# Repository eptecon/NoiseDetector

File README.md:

NoiseDetector: Connected Noise Detector
======

Noise Detector is a simple device for lowering noise levels in the office or public places. It monitors noise level and alarms when it gets too loud. It is also connected to cloud over Wireless LAN for providing noise data for further analytics
It is easy to install and use in every environment.

### Hardware

Noise Detector is based on a MEMS microphone that measures intensity of noise and ESP32 microcontroller that monitors the noise level and sends measured results to cloud.
The user can adjust a threshold for the detection. The Noise Detector can indicate alarms if it is too loud using onboard buzzer and LED.

### Firmware

The firmware consists of a RTOS and applications for measuring and analysing of noise level as well as sending information to cloud. It connects to a cloud and provides noise data over MQTT.

### Usage

No software installation is required. Just turn on and connect to your WLAN Network. Immediately after connecting, the device starts to send the measured noise level 
to the cloud service ([GlueLogics](https://github.com/eptecon/gluelogics)) enabling analytics for your working environment, even without invasive notifications.

---

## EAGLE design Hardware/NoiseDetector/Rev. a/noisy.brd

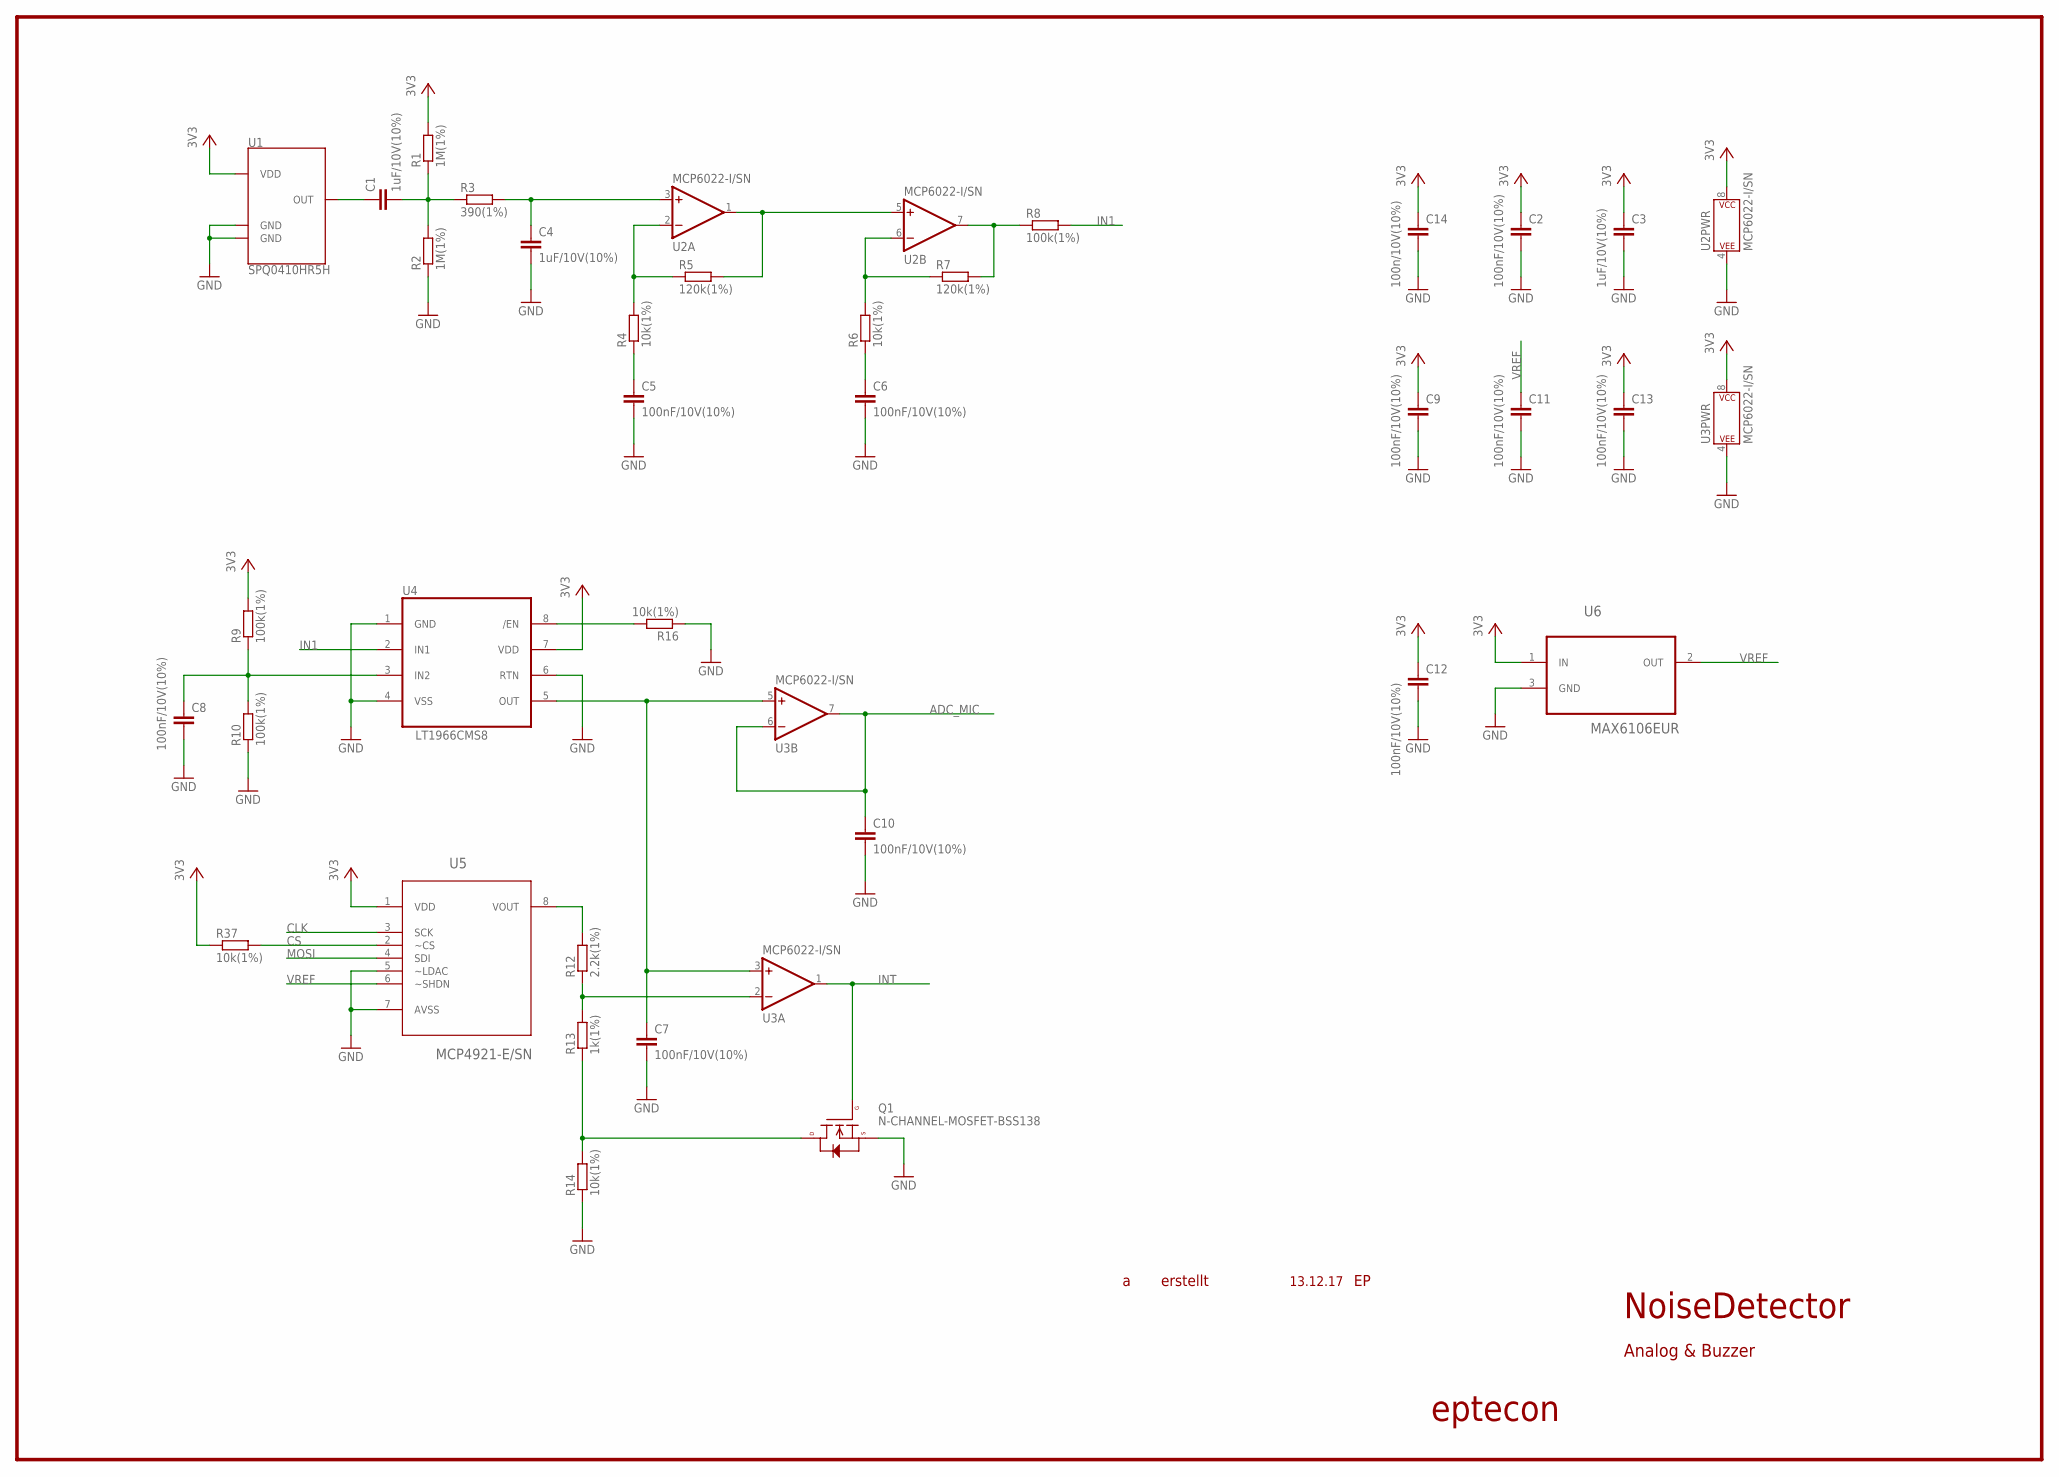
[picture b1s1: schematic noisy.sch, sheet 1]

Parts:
C1, C3, C4: 1uF/10V(10%); C0603
C2, C5, C6, C7, C8, C9, C10, C11, C12, C13: 100nF/10V(10%); C0603
C14: 100n/10V(10%); C0603
Q1: N-CHANNEL-MOSFET-BSS138; SOT23-3
R1, R2: 1M(1%); R0603
R3: 390(1%); R0603
R4, R6, R14, R16, R37: 10k(1%); R0603
R5, R7: 120k(1%); R0603
R8, R9, R10: 100k(1%); R0603
R12: 2.2k(1%); R0603
R13: 1k(1%); R0603
U1: SPQ0410HR5H; SPQ0410HR
U2, U3: MCP6022-I/SN; SOIC08
U4: LT1966CMS8; MSOP8
U5: MCP4921-E/SN; SOIC8-N_MC
U6: MAX6106EUR; SOT23-3

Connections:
3V3: C2.1, C3.1, C9.1, C12.1, C13.1, C14.1, R1.2, R9.2, R37.1, U1.P$1 (VDD), U2.8 (P$V+), U3.8 (P$V+), U4.7 (VDD), U5.1 (VDD), U6.1 (IN); also elsewhere on the board
ADC_MIC: C10.1, U3.6 (-IN), U3.7 (OUT); also elsewhere on the board
CLK: U5.3 (SCK); also elsewhere on the board
CS: R37.2, U5.2 (~CS); also elsewhere on the board
GND: C2.2, C3.2, C4.2, C5.2, C6.2, C7.2, C8.2, C9.2, C10.2, C11.2, C12.2, C13.2, C14.2, Q1.2 (S), R2.1, R10.1, R14.1, R16.1, U1.P$2 (GND), U1.P$3 (GND), U2.4 (P$V-), U3.4 (P$V-), U4.1 (GND), U4.4 (VSS), U4.6 (RTN), U5.5 (~LDAC), U5.7 (AVSS), U6.3 (GND); also elsewhere on the board
IN1: R8.2, U4.2 (IN1)
INT: Q1.1 (G), U3.1 (OUT); also elsewhere on the board
MOSI: U5.4 (SDI); also elsewhere on the board
unnamed: C1.1, U1.P$4 (OUT)
unnamed: C1.2, R1.1, R2.2, R3.1
unnamed: C4.1, R3.2, U2.3 (+IN)
unnamed: R4.2, R5.1, U2.2 (-IN)
unnamed: C5.1, R4.1
unnamed: R5.2, U2.1 (OUT), U2.5 (+IN)
unnamed: R6.2, R7.1, U2.6 (-IN)
unnamed: C6.1, R6.1
unnamed: R7.2, R8.1, U2.7 (OUT)
unnamed: C8.1, R9.1, R10.2, U4.3 (IN2)
unnamed: R12.2, U5.8 (VOUT)
unnamed: R12.1, R13.2, U3.2 (-IN)
unnamed: Q1.3 (D), R13.1, R14.2
unnamed: C7.1, U3.3 (+IN), U3.5 (+IN), U4.5 (OUT)
unnamed: R16.2, U4.8 (/EN)
VREF: C11.1, U5.6 (~SHDN), U6.2 (OUT)

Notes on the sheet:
NoiseDetector
Analog & Buzzer
eptecon
erstellt
13.12.17

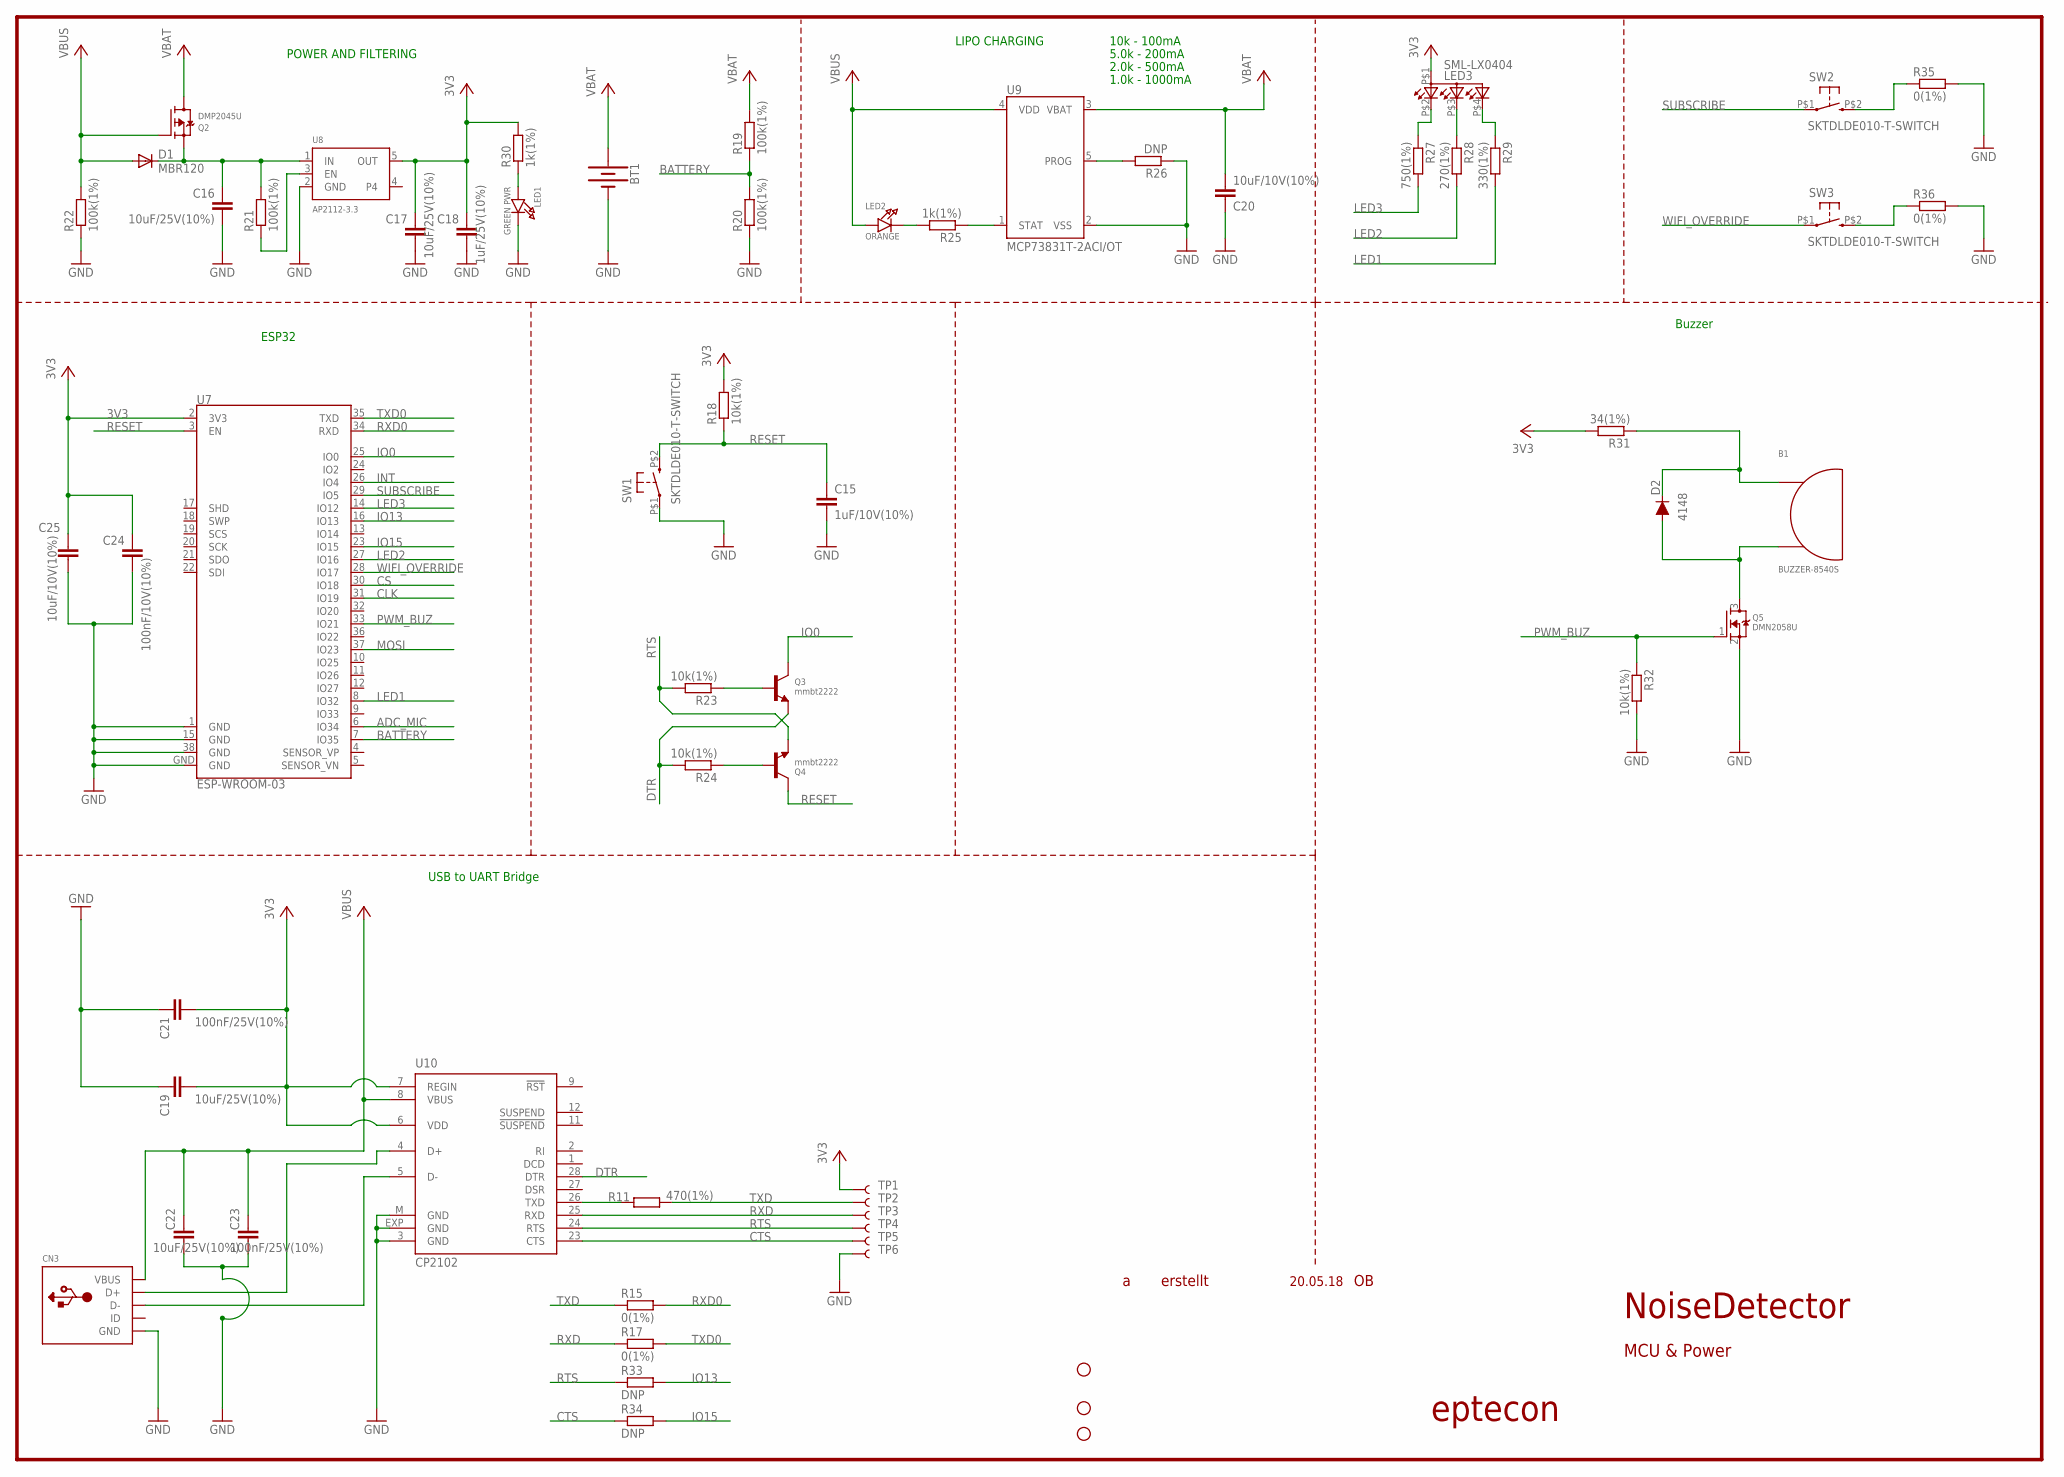
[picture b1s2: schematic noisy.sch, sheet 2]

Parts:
B1: BUZZER-8540S
BT1: BATTERY-AA
C15: 1uF/10V(10%); C0603
C16, C17, C19, C22: 10uF/25V(10%); C0603
C18: 1uF/25V(10%); C0603
C20, C25: 10uF/10V(10%); C0603
C21, C23: 100nF/25V(10%); C0603
C24: 100nF/10V(10%); C0603
CN3: USBMINIBLARGE; USB-MINIB_LARGER
D1: MBR120; SOD123
D2: 4148; SOD-323
H1, H2, H3: STAND-OFF
LED1: GREEN PWR; CHIPLED_0805_NOOUTLINE
LED2: ORANGE; CHIPLED_0805_NOOUTLINE
LED3: SML-LX0404; LED_RGB
Q2: DMP2045U; SOT23-R
Q3, Q4: mmbt2222; SOT23-R
Q5: DMN2058U; SOT23-R
R11: 470(1%); R0603
R15, R17, R35, R36: 0(1%); R0603
R18, R23, R24, R32: 10k(1%); R0603
R19, R20, R21, R22: 100k(1%); R0603
R25, R30: 1k(1%); R0603
R26, R33, R34: DNP; R0603
R27: 750(1%); R0603
R28: 270(1%); R0603
R29: 330(1%); R0603
R31: 34(1%); R0603
SW1, SW2, SW3: SKTDLDE010-T-SWITCH; T-SWITCH-ALPS-2
TP1, TP2, TP3, TP4, TP5, TP6: TEST-POINT3X5; PAD.03X.05
U7: ESP-WROOM-03
U8: AP2112-3.3; SOT23-5
U9: MCP73831T-2ACI/OT; SOT23-5
U10: CP2102; MLP28

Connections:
3V3: C17.1, C18.1, C19.2, C21.2, C24.1, C25.1, LED3.P$1 (A2), R18.2, R30.2, R31.2, TP1.P$1, U7.2 (3V3), U8.5 (OUT), U10.6 (VDD), U10.7 (REGIN); also elsewhere on the board
ADC_MIC: U7.6 (IO34); also elsewhere on the board
BATTERY: R19.1, R20.2, U7.7 (IO35)
CLK: U7.31 (IO19); also elsewhere on the board
CS: U7.30 (IO18); also elsewhere on the board
CTS: R34.1, TP5.P$1, U10.23 (CTS)
DTR: Q3.2 (E), R24.2, U10.28 (DTR)
GND: BT1.GND@1 (-), C15.2, C16.2, C17.2, C18.2, C19.1, C20.1, C21.1, C22.1, C23.1, C24.2, C25.2, CN3.GND, LED1.C, Q5.2 (S), R20.1, R22.1, R26.1, R32.2, R35.2, R36.2, SW1.P$1 (1), TP6.P$1, U7.1 (GND), U7.15 (GND), U7.38 (GND), U7.GND, U8.2 (GND), U9.2 (VSS), U10.3 (GND), U10.EXP (GND), U10.M (GND); also elsewhere on the board
INT: U7.26 (IO4); also elsewhere on the board
IO0: Q3.3 (C), U7.25 (IO0)
IO13: R33.2, U7.16 (IO13)
IO15: R34.2, U7.23 (IO15)
LED1: R29.2, U7.8 (IO32)
LED2: R28.2, U7.27 (IO16)
LED3: R27.2, U7.14 (IO12)
MOSI: U7.37 (IO23); also elsewhere on the board
unnamed: C16.1, D1.C, Q2.2 (S), R21.2, U8.1 (IN)
unnamed: Q4.1 (B), R24.1
unnamed: R11.1, U10.26 (TXD)
unnamed: Q3.1 (B), R23.1
unnamed: CN3.D+, U10.4 (D+)
unnamed: CN3.D-, U10.5 (D-)
unnamed: R35.1, SW2.P$2 (3)
unnamed: R36.1, SW3.P$2 (3)
unnamed: LED3.P$2 (CRED), R27.1
unnamed: R25.1, U9.1 (STAT)
unnamed: LED2.C, R25.2
unnamed: LED3.P$3 (CBLUE), R28.1
unnamed: LED3.P$4 (CGREEN), R29.1
unnamed: R26.2, U9.5 (PROG)
unnamed: R21.1, U8.3 (EN)
unnamed: LED1.A, R30.1
unnamed: B1.PLUS, D2.C, R31.1
unnamed: B1.MINUS, D2.A, Q5.3 (D)
PWM_BUZ: Q5.1 (G), R32.1, U7.33 (IO21)
RESET: C15.1, Q4.3 (C), R18.1, SW1.P$2 (3), U7.3 (EN)
RTS: Q4.2 (E), R23.2, R33.1, TP4.P$1, U10.24 (RTS)
RXD: R17.1, TP3.P$1, U10.25 (RXD)
RXD0: R15.2, U7.34 (RXD)
SUBSCRIBE: SW2.P$1 (1), U7.29 (IO5)
TXD: R11.2, R15.1, TP2.P$1
TXD0: R17.2, U7.35 (TXD)
VBAT: BT1.PWR@1 (+), C20.2, Q2.3 (D), R19.2, U9.3 (VBAT)
VBUS: C22.2, C23.2, CN3.VBUS, D1.A, LED2.A, Q2.1 (G), R22.2, U9.4 (VDD), U10.8 (VBUS)
WIFI_OVERRIDE: SW3.P$1 (1), U7.28 (IO17)

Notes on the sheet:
NoiseDetector
MCU & Power
eptecon
erstellt
20.05.18
ESP32
POWER AND FILTERING
USB to UART Bridge
LIPO CHARGING
10k - 100mA
5.0k - 200mA
2.0k - 500mA
1.0k - 1000mA
Buzzer

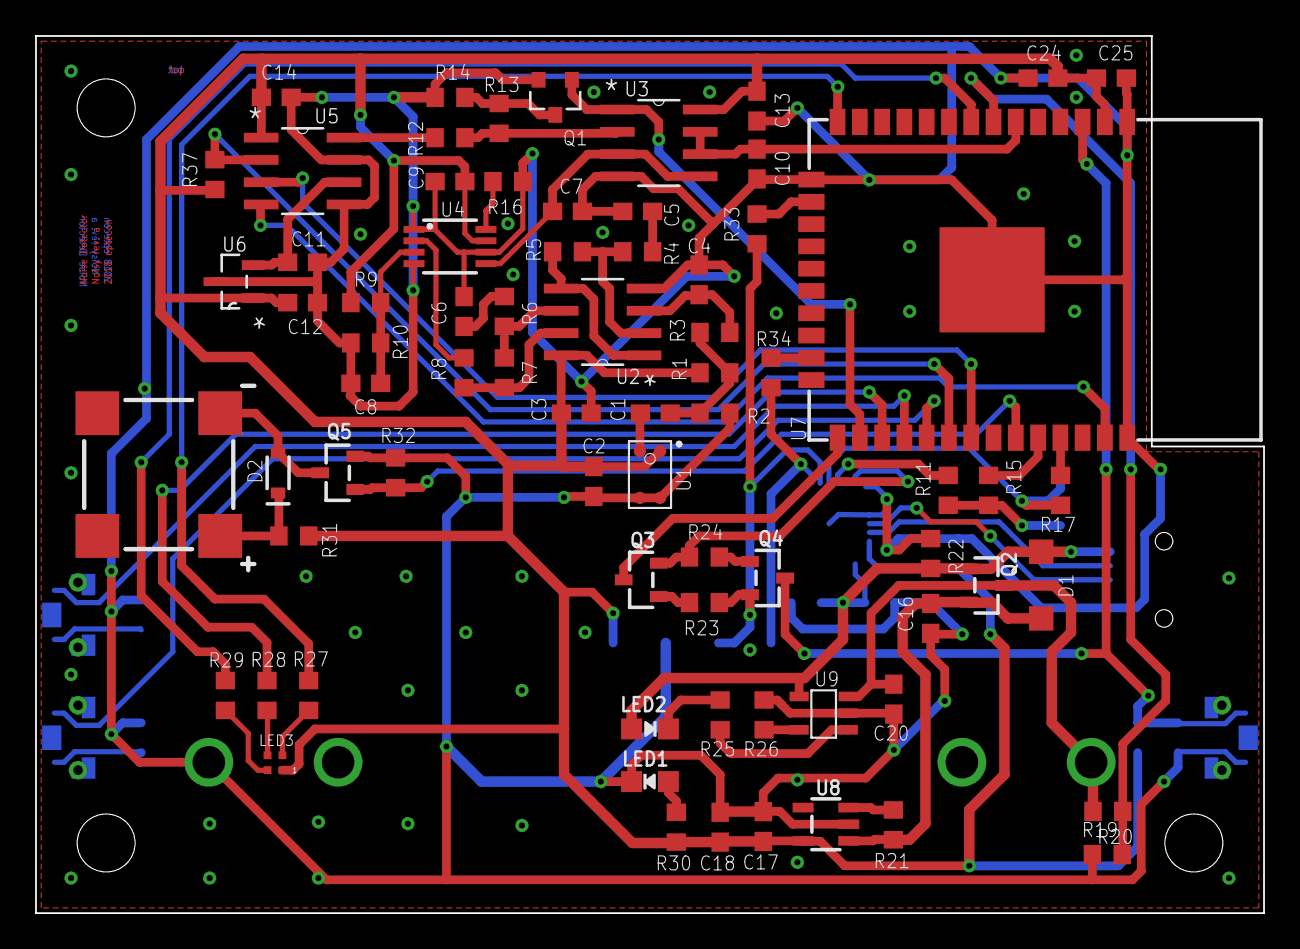
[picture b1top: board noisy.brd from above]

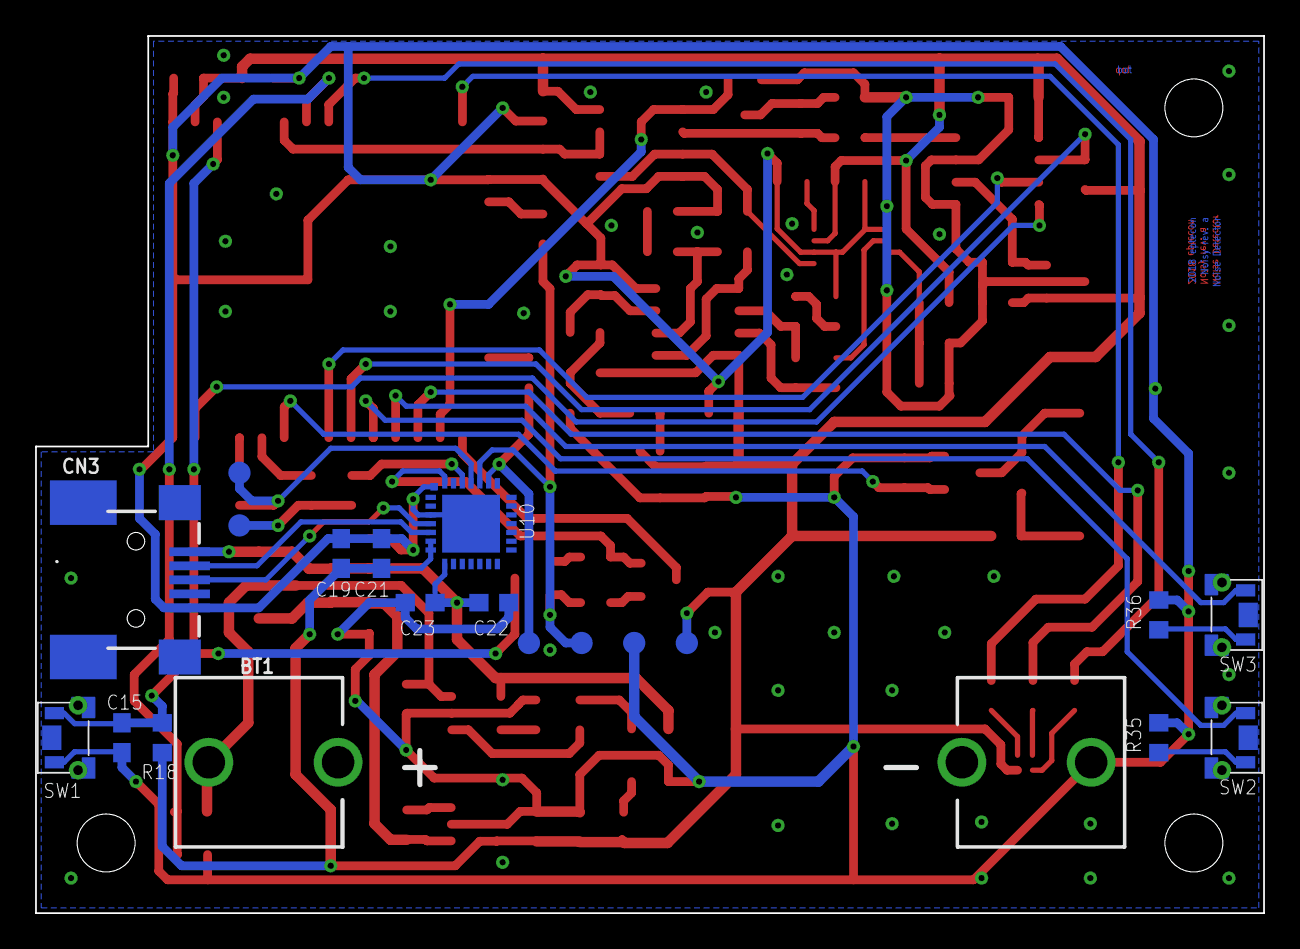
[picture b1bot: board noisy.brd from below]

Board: 2 copper layers, 70.0 x 50.0 mm, 97 parts (20 on the bottom side), 62 nets.

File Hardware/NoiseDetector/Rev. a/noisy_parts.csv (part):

"Part";"Value";"Device";"Package";"Description";"DATASHEET";"DESCRIPTION";"DIGIKEY";"ELEMENT14";"MF";"MPN";"OC_FARNELL";"OC_NEWARK";"OTHER";"PACKAGE";"PROD_ID";"SF_SKU";"SUPPLIER";"URL";"VALUE";
"B1";"BUZZER-8540S";"BUZZER-8540S";"BUZZER-8540S";"";"";"";"";"";"";"";"";"";"";"";"";"";"";"";"";
"BT1";"";"BATTERY-AA";"BATTERY-AA";"Battery - Single Cell";"";"";"";"";"";"";"";"";"";"";"BATT-08316";"PRT-07949";"";"";"";
"C1";"1uF/10V(10%)";"C-EUC0603";"C0603";"CAPACITOR, European symbol";"";"";"";"";"";"";"";"";"";"";"";"";"";"";"";
"C2";"100nF/10V(10%)";"C-EUC0603";"C0603";"CAPACITOR, European symbol";"";"";"";"";"";"";"";"";"";"";"";"";"";"";"";
"C3";"1uF/10V(10%)";"C-EUC0603";"C0603";"CAPACITOR, European symbol";"";"";"";"";"";"";"";"";"";"";"";"";"";"";"";
"C4";"1uF/10V(10%)";"C-EUC0603";"C0603";"CAPACITOR, European symbol";"";"";"";"";"";"";"";"";"";"";"";"";"";"";"";
"C5";"100nF/10V(10%)";"C-EUC0603";"C0603";"CAPACITOR, European symbol";"";"";"";"";"";"";"";"";"";"";"";"";"";"";"";
"C6";"100nF/10V(10%)";"C-EUC0603";"C0603";"CAPACITOR, European symbol";"";"";"";"";"";"";"";"";"";"";"";"";"";"";"";
"C7";"100nF/10V(10%)";"C-EUC0603";"C0603";"CAPACITOR, European symbol";"";"";"";"";"";"";"";"";"";"";"";"";"";"";"";
"C8";"100nF/10V(10%)";"C-EUC0603";"C0603";"CAPACITOR, European symbol";"";"";"";"";"";"";"";"";"";"";"";"";"";"";"";
"C9";"100nF/10V(10%)";"C-EUC0603";"C0603";"CAPACITOR, European symbol";"";"";"";"";"";"";"";"";"";"";"";"";"";"";"";
"C10";"100nF/10V(10%)";"C-EUC0603";"C0603";"CAPACITOR, European symbol";"";"";"";"";"";"";"";"";"";"";"";"";"";"";"";
"C11";"100nF/10V(10%)";"C-EUC0603";"C0603";"CAPACITOR, European symbol";"";"";"";"";"";"";"";"";"";"";"";"";"";"";"";
"C12";"100nF/10V(10%)";"C-EUC0603";"C0603";"CAPACITOR, European symbol";"";"";"";"";"";"";"";"";"";"";"";"";"";"";"";
"C13";"100nF/10V(10%)";"C-EUC0603";"C0603";"CAPACITOR, European symbol";"";"";"";"";"";"";"";"";"";"";"";"";"";"";"";
"C14";"100n/10V(10%)";"C-EUC0603";"C0603";"CAPACITOR, European symbol";"";"";"";"";"";"";"";"";"";"";"";"";"";"";"";
"C15";"1uF/10V(10%)";"C-EUC0603";"C0603";"CAPACITOR, European symbol";"";"";"";"";"";"";"";"";"";"";"";"";"";"";"";
"C16";"10uF/25V(10%)";"C-EUC0603";"C0603";"CAPACITOR, European symbol";"";"";"";"";"";"";"";"";"";"";"";"";"";"";"";
"C17";"10uF/25V(10%)";"C-EUC0603";"C0603";"CAPACITOR, European symbol";"";"";"";"";"";"";"";"";"";"";"";"";"";"";"";
"C18";"1uF/25V(10%)";"C-EUC0603";"C0603";"CAPACITOR, European symbol";"";"";"";"";"";"";"";"";"";"";"";"";"";"";"";
"C19";"10uF/25V(10%)";"C-EUC0603";"C0603";"CAPACITOR, European symbol";"";"";"";"";"";"";"";"";"";"";"";"";"";"";"";
"C20";"10uF/10V(10%)";"C-EUC0603";"C0603";"CAPACITOR, European symbol";"";"";"";"";"";"";"";"";"";"";"";"";"";"";"";
"C21";"100nF/25V(10%)";"C-EUC0603";"C0603";"CAPACITOR, European symbol";"";"";"";"";"";"";"";"";"";"";"";"";"";"";"";
"C22";"10uF/25V(10%)";"C-EUC0603";"C0603";"CAPACITOR, European symbol";"";"";"";"";"";"";"";"";"";"";"";"";"";"";"";
"C23";"100nF/25V(10%)";"C-EUC0603";"C0603";"CAPACITOR, European symbol";"";"";"";"";"";"";"";"";"";"";"";"";"";"";"";
"C24";"100nF/10V(10%)";"C-EUC0603";"C0603";"CAPACITOR, European symbol";"";"";"";"";"";"";"";"";"";"";"";"";"";"";"";
"C25";"10uF/10V(10%)";"C-EUC0603";"C0603";"CAPACITOR, European symbol";"";"";"";"";"";"";"";"";"";"";"";"";"";"";"";
"CN3";"";"USBMINIBLARGE";"USB-MINIB_LARGER";"USB Connectors";"";"";"";"";"";"";"";"";"";"";"";"";"";"";"";
"D1";"MBR120";"MBR0520LT";"SOD123";"SCHOTTKY BARRIER RECTIFIER";"";"";"";"";"";"";"";"";"";"";"";"";"";"";"";
"D2";"4148";"DIODE-BAS16J";"SOD-323";"Diode";"";"";"";"";"";"";"";"";"";"";"DIO-09646";"";"";"";"250mA/100V";
"H1";"STAND-OFF";"STAND-OFF";"STAND-OFF";"Stand Off";"";"";"";"";"";"";"";"";"";"";"";"";"";"";"";
"H2";"STAND-OFF";"STAND-OFF";"STAND-OFF";"Stand Off";"";"";"";"";"";"";"";"";"";"";"";"";"";"";"";
"H3";"STAND-OFF";"STAND-OFF";"STAND-OFF";"Stand Off";"";"";"";"";"";"";"";"";"";"";"";"";"";"";"";
"LED1";"GREEN PWR";"LED0805_NOOUTLINE";"CHIPLED_0805_NOOUTLINE";"LED";"";"";"";"";"";"";"";"";"";"";"";"";"";"";"";
"LED2";"ORANGE";"LED0805_NOOUTLINE";"CHIPLED_0805_NOOUTLINE";"LED";"";"";"";"";"";"";"";"";"";"";"";"";"";"";"";
"LED3";"SML-LX0404";"SML-LX0404";"LED_RGB";"";"";"";"";"";"";"";"";"";"";"";"";"";"";"";"";
"Q1";"N-CHANNEL-MOSFET-BSS138";"N-CHANNEL-MOSFET-BSS138";"SOT23-3";"N-Channel MOSFET Mode Field Effect Transistor";"http://www.fairchildsemi.com/ds/BS/BSS138.pdf";"";"BSS138TR-ND";"2323154";"";"";"";"";"";"";"";"";"";"http://au.element14.com/fairchild-semiconductor/bss138/mosfe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";"";
"Q2";"DMP2045U";"MOSFET-P";"SOT23-R";"P-Channel Mosfet";"";"";"";"";"";"";"";"";"";"";"";"";"";"";"";
"Q3";"mmbt2222";"TRANSISTOR_NPN";"SOT23-R";"NPN Transistor";"";"";"";"";"";"";"";"";"";"";"";"";"";"";"";
"Q4";"mmbt2222";"TRANSISTOR_NPN";"SOT23-R";"NPN Transistor";"";"";"";"";"";"";"";"";"";"";"";"";"";"";"";
"Q5";"DMN2058U";"MOSFET-NREFLOW";"SOT23-R";"N-Channel Mosfet";"";"";"";"";"";"";"";"";"";"";"";"";"";"";"";
"R1";"1M(1%)";"R-EU_R0603";"R0603";"RESISTOR, European symbol";"";"";"";"";"";"";"";"";"";"";"";"";"";"";"";
"R2";"1M(1%)";"R-EU_R0603";"R0603";"RESISTOR, European symbol";"";"";"";"";"";"";"";"";"";"";"";"";"";"";"";
"R3";"390(1%)";"R-EU_R0603";"R0603";"RESISTOR, European symbol";"";"";"";"";"";"";"";"";"";"";"";"";"";"";"";
"R4";"10k(1%)";"R-EU_R0603";"R0603";"RESISTOR, European symbol";"";"";"";"";"";"";"";"";"";"";"";"";"";"";"";
"R5";"120k(1%)";"R-EU_R0603";"R0603";"RESISTOR, European symbol";"";"";"";"";"";"";"";"";"";"";"";"";"";"";"";
"R6";"10k(1%)";"R-EU_R0603";"R0603";"RESISTOR, European symbol";"";"";"";"";"";"";"";"";"";"";"";"";"";"";"";
"R7";"120k(1%)";"R-EU_R0603";"R0603";"RESISTOR, European symbol";"";"";"";"";"";"";"";"";"";"";"";"";"";"";"";
"R8";"100k(1%)";"R-EU_R0603";"R0603";"RESISTOR, European symbol";"";"";"";"";"";"";"";"";"";"";"";"";"";"";"";
"R9";"100k(1%)";"R-EU_R0603";"R0603";"RESISTOR, European symbol";"";"";"";"";"";"";"";"";"";"";"";"";"";"";"";
"R10";"100k(1%)";"R-EU_R0603";"R0603";"RESISTOR, European symbol";"";"";"";"";"";"";"";"";"";"";"";"";"";"";"";
"R11";"470(1%)";"R-EU_R0603";"R0603";"RESISTOR, European symbol";"";"";"";"";"";"";"";"";"";"";"";"";"";"";"";
"R12";"2.2k(1%)";"R-EU_R0603";"R0603";"RESISTOR, European symbol";"";"";"";"";"";"";"";"";"";"";"";"";"";"";"";
"R13";"1k(1%)";"R-EU_R0603";"R0603";"RESISTOR, European symbol";"";"";"";"";"";"";"";"";"";"";"";"";"";"";"";
"R14";"10k(1%)";"R-EU_R0603";"R0603";"RESISTOR, European symbol";"";"";"";"";"";"";"";"";"";"";"";"";"";"";"";
"R15";"0(1%)";"R-EU_R0603";"R0603";"RESISTOR, European symbol";"";"";"";"";"";"";"";"";"";"";"";"";"";"";"";
"R16";"10k(1%)";"R-EU_R0603";"R0603";"RESISTOR, European symbol";"";"";"";"";"";"";"";"";"";"";"";"";"";"";"";
"R17";"0(1%)";"R-EU_R0603";"R0603";"RESISTOR, European symbol";"";"";"";"";"";"";"";"";"";"";"";"";"";"";"";
"R18";"10k(1%)";"R-EU_R0603";"R0603";"RESISTOR, European symbol";"";"";"";"";"";"";"";"";"";"";"";"";"";"";"";
"R19";"100k(1%)";"R-EU_R0603";"R0603";"RESISTOR, European symbol";"";"";"";"";"";"";"";"";"";"";"";"";"";"";"";
"R20";"100k(1%)";"R-EU_R0603";"R0603";"RESISTOR, European symbol";"";"";"";"";"";"";"";"";"";"";"";"";"";"";"";
"R21";"100k(1%)";"R-EU_R0603";"R0603";"RESISTOR, European symbol";"";"";"";"";"";"";"";"";"";"";"";"";"";"";"";
"R22";"100k(1%)";"R-EU_R0603";"R0603";"RESISTOR, European symbol";"";"";"";"";"";"";"";"";"";"";"";"";"";"";"";
"R23";"10k(1%)";"R-EU_R0603";"R0603";"RESISTOR, European symbol";"";"";"";"";"";"";"";"";"";"";"";"";"";"";"";
"R24";"10k(1%)";"R-EU_R0603";"R0603";"RESISTOR, European symbol";"";"";"";"";"";"";"";"";"";"";"";"";"";"";"";
"R25";"1k(1%)";"R-EU_R0603";"R0603";"RESISTOR, European symbol";"";"";"";"";"";"";"";"";"";"";"";"";"";"";"";
"R26";"DNP";"R-EU_R0603";"R0603";"RESISTOR, European symbol";"";"";"";"";"";"";"";"";"";"";"";"";"";"";"";
"R27";"750(1%)";"R-EU_R0603";"R0603";"RESISTOR, European symbol";"";"";"";"";"";"";"";"";"";"";"";"";"";"";"";
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
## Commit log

2021-05-29 readme update
2021-06-28 license added
2021-09-04 Update LICENSE

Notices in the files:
parts and their libraries:
GeekAmmo: Licensing:Creative Commons ShareAlike 4.0 International - https://creativecommons.org/licenses/by-sa/4.0
microbuilder: This work is placed in the public domain, and may be freely used for commercial and non-commercial work with the following conditions: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
